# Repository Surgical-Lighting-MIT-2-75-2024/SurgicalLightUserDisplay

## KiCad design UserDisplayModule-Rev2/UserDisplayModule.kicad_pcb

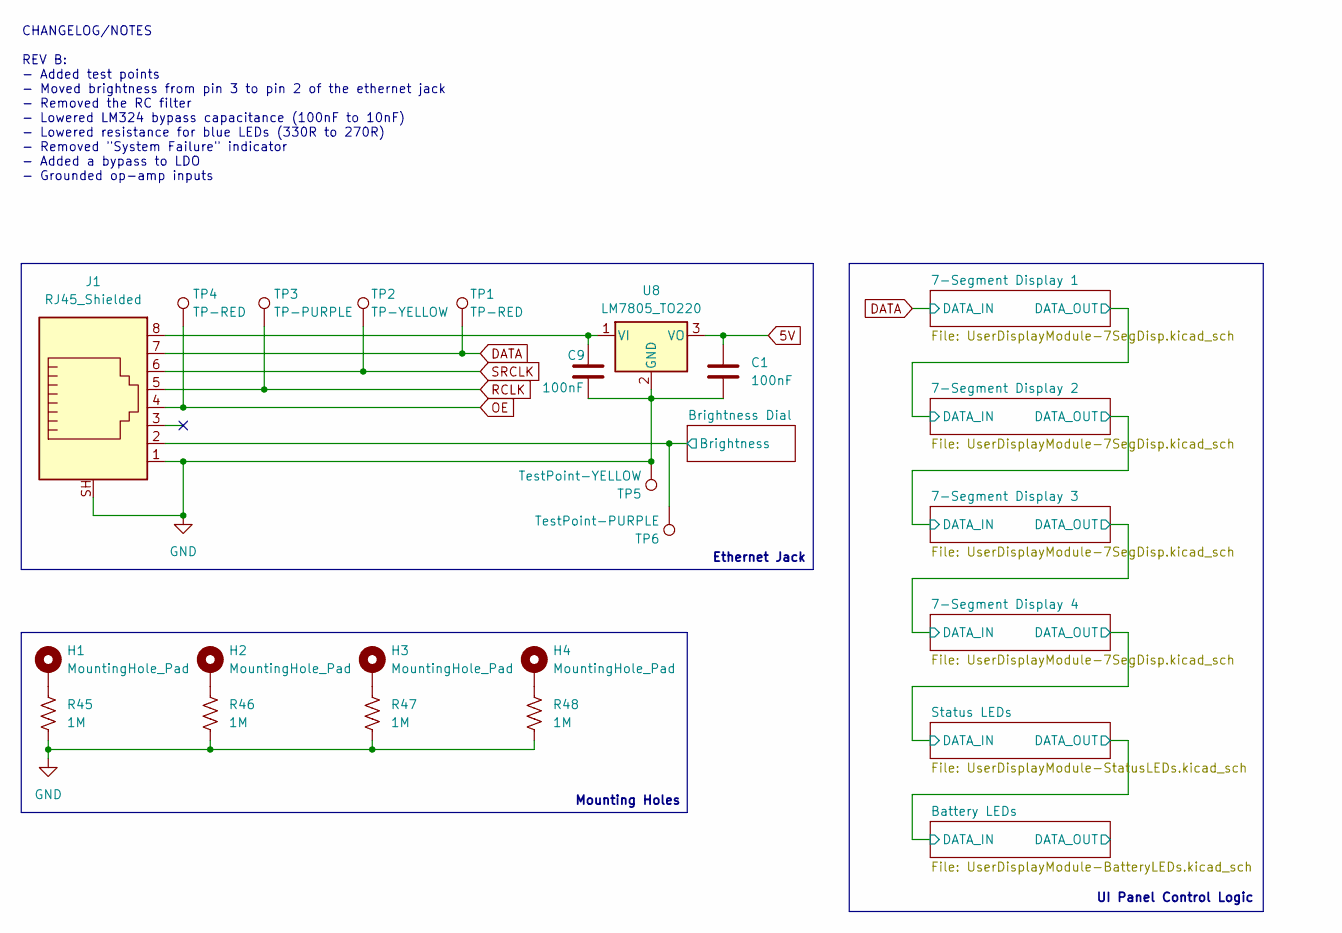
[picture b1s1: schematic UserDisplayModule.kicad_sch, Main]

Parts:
C1, C9: 100nF; C_0805_2012Metric
H1, H2, H3, H4: MountingHole_Pad; MountingHole_3.2mm_M3_Pad
J1: RJ45_Shielded; RJ45_Shielded_EthernetJack; Digikey PN AE10399-ND
R45, R46, R47, R48: 1M; R_0805_2012Metric; Digikey PN RMCF0805FT1M00CT-ND
TP1, TP4: TP-RED; TestPoint_Keystone_5000-5004_Miniature; Digikey PN 36-5260-ND
TP2: TP-YELLOW; TestPoint_Keystone_5000-5004_Miniature; Digikey PN 36-5264-ND
TP3: TP-PURPLE; TestPoint_Keystone_5000-5004_Miniature; Digikey PN 36-5269-ND
TP5: TestPoint-YELLOW; TestPoint_Keystone_5000-5004_Miniature; Digikey PN 36-5264-ND
TP6: TestPoint-PURPLE; TestPoint_Keystone_5000-5004_Miniature; Digikey PN 36-5269-ND
U8: LM7805_TO220; TO-220-3_Vertical; Digikey PN 2129-NJM7805FA-ND

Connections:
5V: C1.1, U8.3 (VO); also elsewhere on the board
/Brightness Dial/Brightness: J1.2, TP6.1; also elsewhere on the board
DATA: J1.7, TP1.1; also elsewhere on the board
GND: C1.2, C9.2, J1.1, J1.SH, R45.2, R46.2, R47.2, R48.2, TP5.1, U8.2 (GND); also elsewhere on the board
unnamed: H1.1, R45.1
unnamed: H2.1, R46.1
unnamed: H3.1, R47.1
unnamed: H4.1, R48.1
unnamed: C9.1, J1.8, U8.1 (VI)
OE: J1.4, TP4.1; also elsewhere on the board
RCLK: J1.5, TP3.1; also elsewhere on the board
SRCLK: J1.6, TP2.1; also elsewhere on the board

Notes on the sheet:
Mounting Holes
Ethernet Jack
UI Panel Control Logic
CHANGELOG/NOTES REV B: - Added test points - Moved brightness from pin 3 to pin 2 of the ethernet jack - Removed the RC filter - Lowered LM324 bypass capacitance (100nF to 10nF) - Lowered resistance for blue LEDs (330R to 270R) - Removed "System Failure" indicator - Added a bypass to LDO - Grounded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

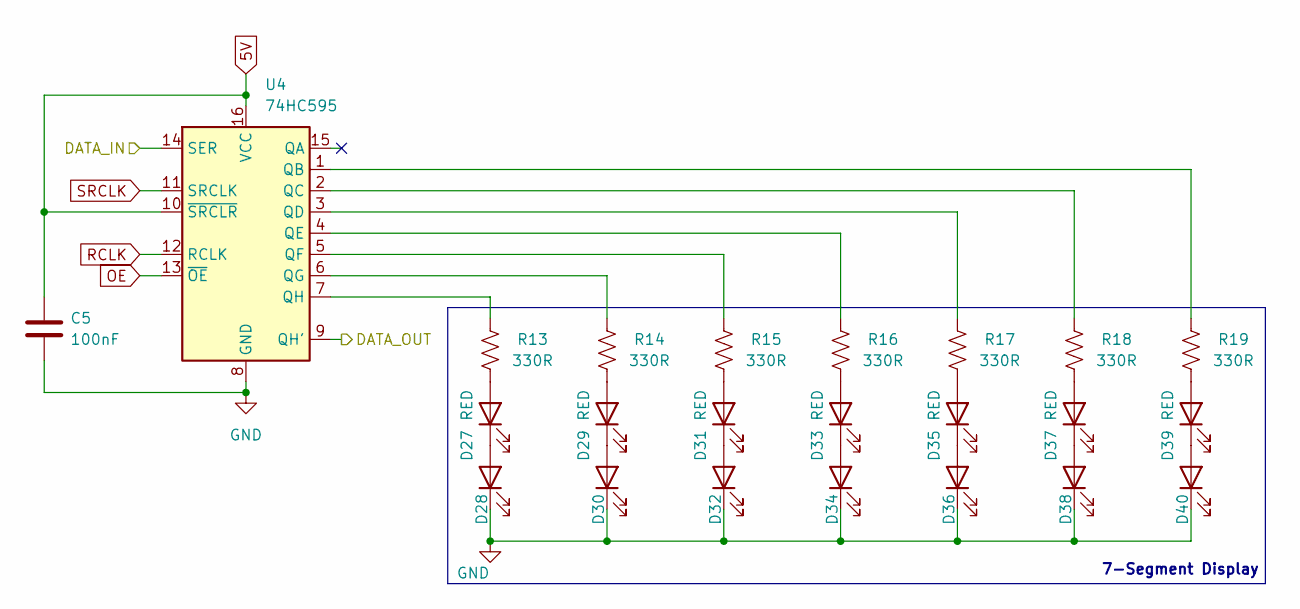
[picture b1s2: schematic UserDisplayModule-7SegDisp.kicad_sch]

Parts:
C5: 100nF; C_0805_2012Metric; Digikey PN 1276-1003-1-ND
D27, D28, D29, D30, D31, D32, D33, D34, D35, D36, D37, D38, D39, D40: RED; LED_0805_2012Metric; Digikey PN 732-4984-1-ND
R13, R14, R15, R16, R17, R18, R19: 330R; R_0805_2012Metric; Digikey PN RMCF0805FT330RCT-ND
U4: 74HC595; CD74HC595E; Digikey PN 296-1600-5-ND

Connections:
5V: C5.1, U4.10 (~SRCLR), U4.16 (VCC); also elsewhere on the board
/7-Segment Display 1/DATA_OUT: U4.9 (QH'); also elsewhere on the board
DATA: U4.14 (SER); also elsewhere on the board
GND: C5.2, D28.1 (K), D30.1 (K), D32.1 (K), D34.1 (K), D36.1 (K), D38.1 (K), D40.1 (K), U4.8 (GND); also elsewhere on the board
unnamed: D27.2 (A), R13.2
unnamed: D27.1 (K), D28.2 (A)
unnamed: D29.2 (A), R14.2
unnamed: D29.1 (K), D30.2 (A)
unnamed: D31.2 (A), R15.2
unnamed: D31.1 (K), D32.2 (A)
unnamed: D33.2 (A), R16.2
unnamed: D33.1 (K), D34.2 (A)
unnamed: D35.2 (A), R17.2
unnamed: D35.1 (K), D36.2 (A)
unnamed: D37.2 (A), R18.2
unnamed: D37.1 (K), D38.2 (A)
unnamed: D39.2 (A), R19.2
unnamed: D39.1 (K), D40.2 (A)
unnamed: R19.1, U4.1 (QB)
unnamed: R18.1, U4.2 (QC)
unnamed: R17.1, U4.3 (QD)
unnamed: R16.1, U4.4 (QE)
unnamed: R15.1, U4.5 (QF)
unnamed: R14.1, U4.6 (QG)
unnamed: R13.1, U4.7 (QH)
OE: U4.13 (~OE); also elsewhere on the board
RCLK: U4.12 (RCLK); also elsewhere on the board
SRCLK: U4.11 (SRCLK); also elsewhere on the board

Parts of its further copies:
C6, C7, C8: 100nF; C_0805_2012Metric; Digikey PN 1276-1003-1-ND
D46, D47, D48, D49, D50, D51, D52, D53, D54, D55, D56, D57, D58, D59, D60, D61, D62, D63, D64, D65, D66, D67, D68, D69, D70, D71, D72, D73, D74, D75, D76, D77, D78, D79, D80, D81, D82, D83, D84, D85, D86, D87: RED; LED_0805_2012Metric; Digikey PN 732-4984-1-ND
R24, R25, R26, R27, R28, R29, R30, R31, R32, R33, R34, R35, R36, R37, R38, R39, R40, R41, R42, R43, R44: 330R; R_0805_2012Metric; Digikey PN RMCF0805FT330RCT-ND
U3, U6, U7: 74HC595; CD74HC595E; Digikey PN 296-1600-5-ND

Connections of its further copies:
5V: C6.1, C7.1, C8.1, U3.10 (~SRCLR), U3.16 (VCC), U6.10 (~SRCLR), U6.16 (VCC), U7.10 (~SRCLR), U7.16 (VCC); also elsewhere on the board
/7-Segment Display 1/DATA_OUT: U3.14 (SER); also elsewhere on the board
/7-Segment Display 2/DATA_OUT: U3.9 (QH'), U6.14 (SER)
/7-Segment Display 3/DATA_OUT: U6.9 (QH'), U7.14 (SER)
/7-Segment Display 4/DATA_OUT: U7.9 (QH'); also elsewhere on the board
GND: C6.2, C7.2, C8.2, D47.1 (K), D49.1 (K), D51.1 (K), D53.1 (K), D55.1 (K), D57.1 (K), D59.1 (K), D61.1 (K), D63.1 (K), D65.1 (K), D67.1 (K), D69.1 (K), D71.1 (K), D73.1 (K), D75.1 (K), D77.1 (K), D79.1 (K), D81.1 (K), D83.1 (K), D85.1 (K), D87.1 (K), U3.8 (GND), U6.8 (GND), U7.8 (GND); also elsewhere on the board
unnamed: D46.2 (A), R24.2
unnamed: D46.1 (K), D47.2 (A)
unnamed: D48.2 (A), R25.2
unnamed: D48.1 (K), D49.2 (A)
unnamed: D50.2 (A), R26.2
unnamed: D50.1 (K), D51.2 (A)
unnamed: D52.2 (A), R27.2
unnamed: D52.1 (K), D53.2 (A)
unnamed: D54.2 (A), R28.2
unnamed: D54.1 (K), D55.2 (A)
unnamed: D56.2 (A), R29.2
unnamed: D56.1 (K), D57.2 (A)
unnamed: D58.2 (A), R30.2
unnamed: D58.1 (K), D59.2 (A)
unnamed: D60.2 (A), R31.2
unnamed: D60.1 (K), D61.2 (A)
unnamed: D62.2 (A), R32.2
unnamed: D62.1 (K), D63.2 (A)
unnamed: D64.2 (A), R33.2
unnamed: D64.1 (K), D65.2 (A)
unnamed: D66.2 (A), R34.2
unnamed: D66.1 (K), D67.2 (A)
unnamed: D68.2 (A), R35.2
unnamed: D68.1 (K), D69.2 (A)
unnamed: D70.2 (A), R36.2
unnamed: D70.1 (K), D71.2 (A)
unnamed: D72.2 (A), R37.2
unnamed: D72.1 (K), D73.2 (A)
unnamed: D74.2 (A), R38.2
unnamed: D74.1 (K), D75.2 (A)
unnamed: D76.2 (A), R39.2
unnamed: D76.1 (K), D77.2 (A)
unnamed: D78.2 (A), R40.2
unnamed: D78.1 (K), D79.2 (A)
unnamed: D80.2 (A), R41.2
unnamed: D80.1 (K), D81.2 (A)
unnamed: D82.2 (A), R42.2
unnamed: D82.1 (K), D83.2 (A)
unnamed: D84.2 (A), R43.2
unnamed: D84.1 (K), D85.2 (A)
unnamed: D86.2 (A), R44.2
unnamed: D86.1 (K), D87.2 (A)
unnamed: R30.1, U3.1 (QB)
unnamed: R29.1, U3.2 (QC)
unnamed: R28.1, U3.3 (QD)
unnamed: R27.1, U3.4 (QE)
unnamed: R26.1, U3.5 (QF)
unnamed: R25.1, U3.6 (QG)
unnamed: R24.1, U3.7 (QH)
unnamed: R37.1, U6.1 (QB)
unnamed: R36.1, U6.2 (QC)
unnamed: R35.1, U6.3 (QD)
unnamed: R34.1, U6.4 (QE)
unnamed: R33.1, U6.5 (QF)
unnamed: R32.1, U6.6 (QG)
unnamed: R31.1, U6.7 (QH)
unnamed: R44.1, U7.1 (QB)
unnamed: R43.1, U7.2 (QC)
unnamed: R42.1, U7.3 (QD)
unnamed: R41.1, U7.4 (QE)
unnamed: R40.1, U7.5 (QF)
unnamed: R39.1, U7.6 (QG)
unnamed: R38.1, U7.7 (QH)
OE: U3.13 (~OE), U6.13 (~OE), U7.13 (~OE); also elsewhere on the board
RCLK: U3.12 (RCLK), U6.12 (RCLK), U7.12 (RCLK); also elsewhere on the board
SRCLK: U3.11 (SRCLK), U6.11 (SRCLK), U7.11 (SRCLK); also elsewhere on the board

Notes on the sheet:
7-Segment Display

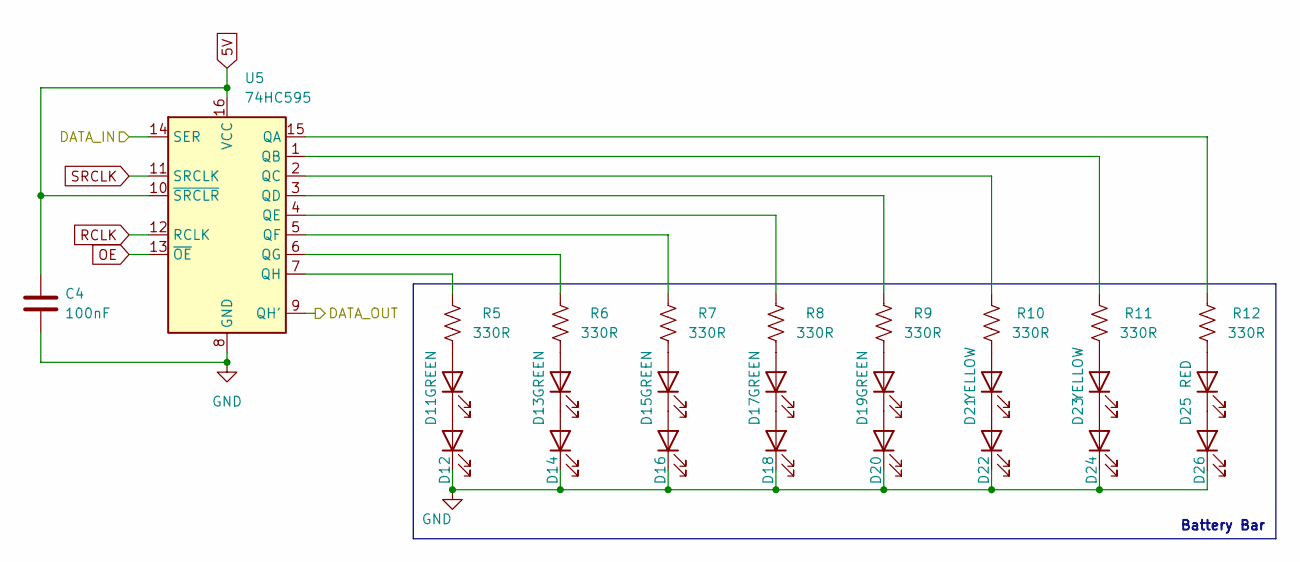
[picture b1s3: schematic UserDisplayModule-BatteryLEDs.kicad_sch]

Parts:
C4: 100nF; C_0805_2012Metric; Digikey PN 1276-1003-1-ND
D11, D12, D13, D14, D15, D16, D17, D18, D19, D20: GREEN; LED_0805_2012Metric; Digikey PN 732-4983-1-ND
D21, D22, D23, D24: YELLOW; LED_0805_2012Metric; Digikey PN 732-4987-1-ND
D25, D26: RED; LED_0805_2012Metric; Digikey PN 732-4984-1-ND
R5, R6, R7, R8, R9, R10, R11, R12: 330R; R_0805_2012Metric; Digikey PN RMCF0805FT330RCT-ND
U5: 74HC595; CD74HC595E; Digikey PN 296-1600-5-ND

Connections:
5V: C4.1, U5.10 (~SRCLR), U5.16 (VCC); also elsewhere on the board
/Battery LEDs/DATA_IN: U5.14 (SER); also elsewhere on the board
/Battery LEDs/DATA_OUT: U5.9 (QH')
GND: C4.2, D12.1 (K), D14.1 (K), D16.1 (K), D18.1 (K), D20.1 (K), D22.1 (K), D24.1 (K), D26.1 (K), U5.8 (GND); also elsewhere on the board
unnamed: D11.2 (A), R5.2
unnamed: D11.1 (K), D12.2 (A)
unnamed: D13.2 (A), R6.2
unnamed: D13.1 (K), D14.2 (A)
unnamed: D15.2 (A), R7.2
unnamed: D15.1 (K), D16.2 (A)
unnamed: D17.2 (A), R8.2
unnamed: D17.1 (K), D18.2 (A)
unnamed: D19.2 (A), R9.2
unnamed: D19.1 (K), D20.2 (A)
unnamed: D21.2 (A), R10.2
unnamed: D21.1 (K), D22.2 (A)
unnamed: D23.2 (A), R11.2
unnamed: D23.1 (K), D24.2 (A)
unnamed: D25.2 (A), R12.2
unnamed: D25.1 (K), D26.2 (A)
unnamed: R12.1, U5.15 (QA)
unnamed: R11.1, U5.1 (QB)
unnamed: R10.1, U5.2 (QC)
unnamed: R9.1, U5.3 (QD)
unnamed: R8.1, U5.4 (QE)
unnamed: R7.1, U5.5 (QF)
unnamed: R6.1, U5.6 (QG)
unnamed: R5.1, U5.7 (QH)
OE: U5.13 (~OE); also elsewhere on the board
RCLK: U5.12 (RCLK); also elsewhere on the board
SRCLK: U5.11 (SRCLK); also elsewhere on the board

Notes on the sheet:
Battery Bar

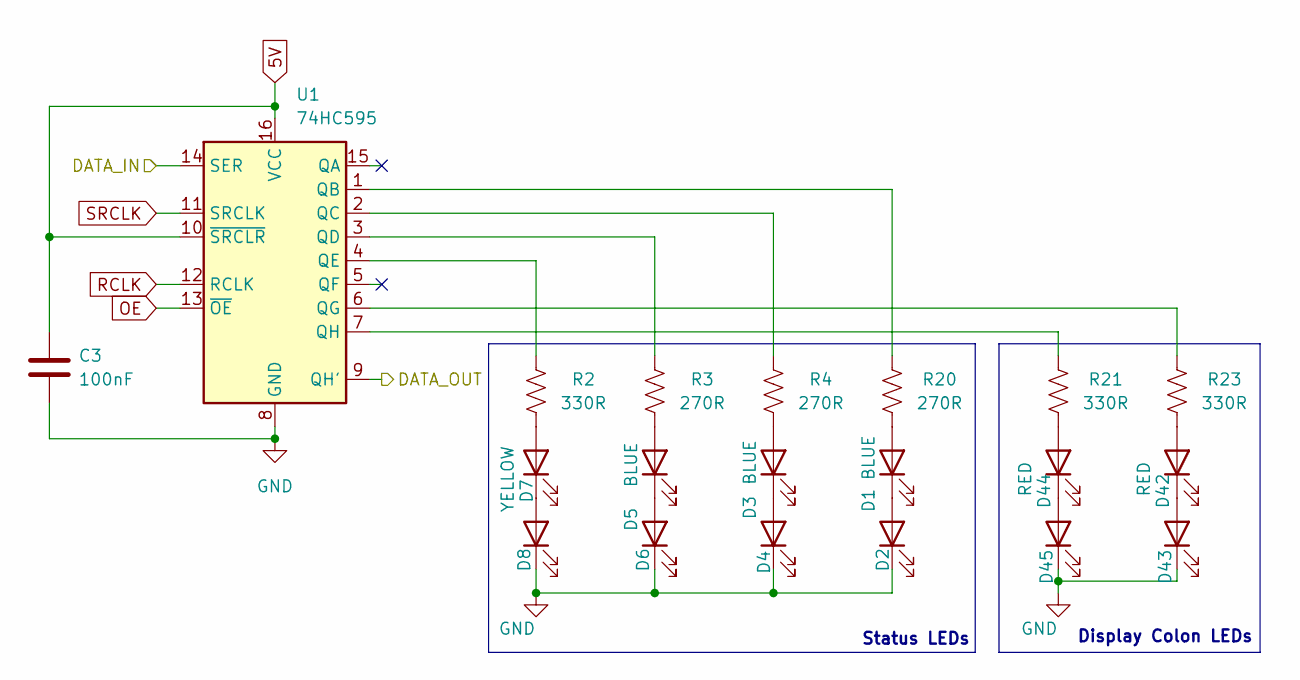
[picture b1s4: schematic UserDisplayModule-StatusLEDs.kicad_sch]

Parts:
C3: 100nF; C_0805_2012Metric; Digikey PN 1276-1003-1-ND
D1, D2, D3, D4, D5, D6: BLUE; LED_0805_2012Metric; Digikey PN 732-4982-1-ND
D7, D8: YELLOW; LED_0805_2012Metric; Digikey PN 732-4987-1-ND
D42, D43, D44, D45: RED; LED_0805_2012Metric; Digikey PN 732-4984-1-ND
R2, R21, R23: 330R; R_0805_2012Metric; Digikey PN RMCF0805FT330RCT-ND
R3, R4, R20: 270R; R_0805_2012Metric; Digikey PN RMCF0805FT330RCT-ND
U1: 74HC595; CD74HC595E; Digikey PN 296-1600-5-ND

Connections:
5V: C3.1, U1.10 (~SRCLR), U1.16 (VCC); also elsewhere on the board
/7-Segment Display 4/DATA_OUT: U1.14 (SER); also elsewhere on the board
/Battery LEDs/DATA_IN: U1.9 (QH'); also elsewhere on the board
GND: C3.2, D2.1 (K), D4.1 (K), D6.1 (K), D8.1 (K), D43.1 (K), D45.1 (K), U1.8 (GND); also elsewhere on the board
unnamed: D1.2 (A), R20.2
unnamed: D1.1 (K), D2.2 (A)
unnamed: D3.2 (A), R4.2
unnamed: D3.1 (K), D4.2 (A)
unnamed: D5.2 (A), R3.2
unnamed: D5.1 (K), D6.2 (A)
unnamed: D7.2 (A), R2.2
unnamed: D7.1 (K), D8.2 (A)
unnamed: D42.2 (A), R23.2
unnamed: D42.1 (K), D43.2 (A)
unnamed: D44.2 (A), R21.2
unnamed: D44.1 (K), D45.2 (A)
unnamed: R20.1, U1.1 (QB)
unnamed: R4.1, U1.2 (QC)
unnamed: R3.1, U1.3 (QD)
unnamed: R2.1, U1.4 (QE)
unnamed: R23.1, U1.6 (QG)
unnamed: R21.1, U1.7 (QH)
OE: U1.13 (~OE); also elsewhere on the board
RCLK: U1.12 (RCLK); also elsewhere on the board
SRCLK: U1.11 (SRCLK); also elsewhere on the board

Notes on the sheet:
Status LEDs
Display Colon LEDs

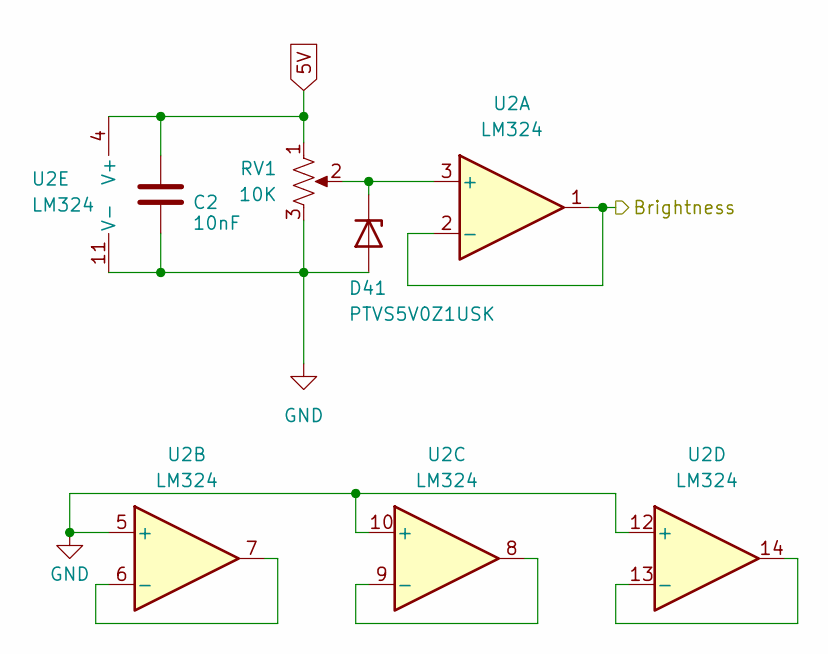
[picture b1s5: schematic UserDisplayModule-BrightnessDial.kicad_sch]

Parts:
C2: 10nF; C_0805_2012Metric; Digikey PN 1276-1003-1-ND
D41: PTVS5V0Z1USK; Nexperia_DSN1608-2_1.6x0.8mm; Digikey PN 1727-2742-1-ND
RV1: 10K; Potentiometer_TT_P0915N; Digikey PN 987-1649-ND
U2: LM324; DIP-14_W7.62mm; Digikey PN 296-1391-5-ND

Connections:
5V: C2.1, RV1.1, U2.4 (V+); also elsewhere on the board
/Brightness Dial/Brightness: U2.1, U2.2 (-); also elsewhere on the board
GND: C2.2, D41.2 (A), RV1.3, U2.5 (+), U2.10 (+), U2.11 (V-), U2.12 (+); also elsewhere on the board
unnamed: D41.1 (K), RV1.2, U2.3 (+)
unnamed: U2.6 (-), U2.7
unnamed: U2.8, U2.9 (-)
unnamed: U2.13 (-), U2.14

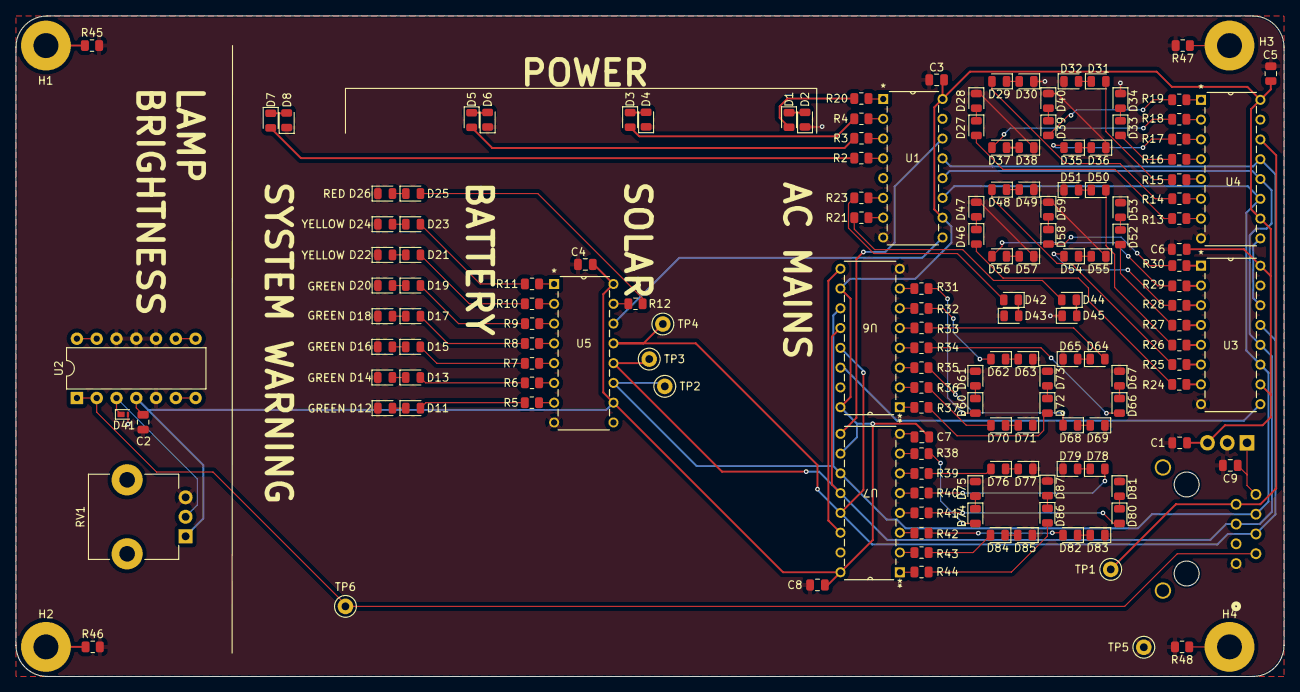
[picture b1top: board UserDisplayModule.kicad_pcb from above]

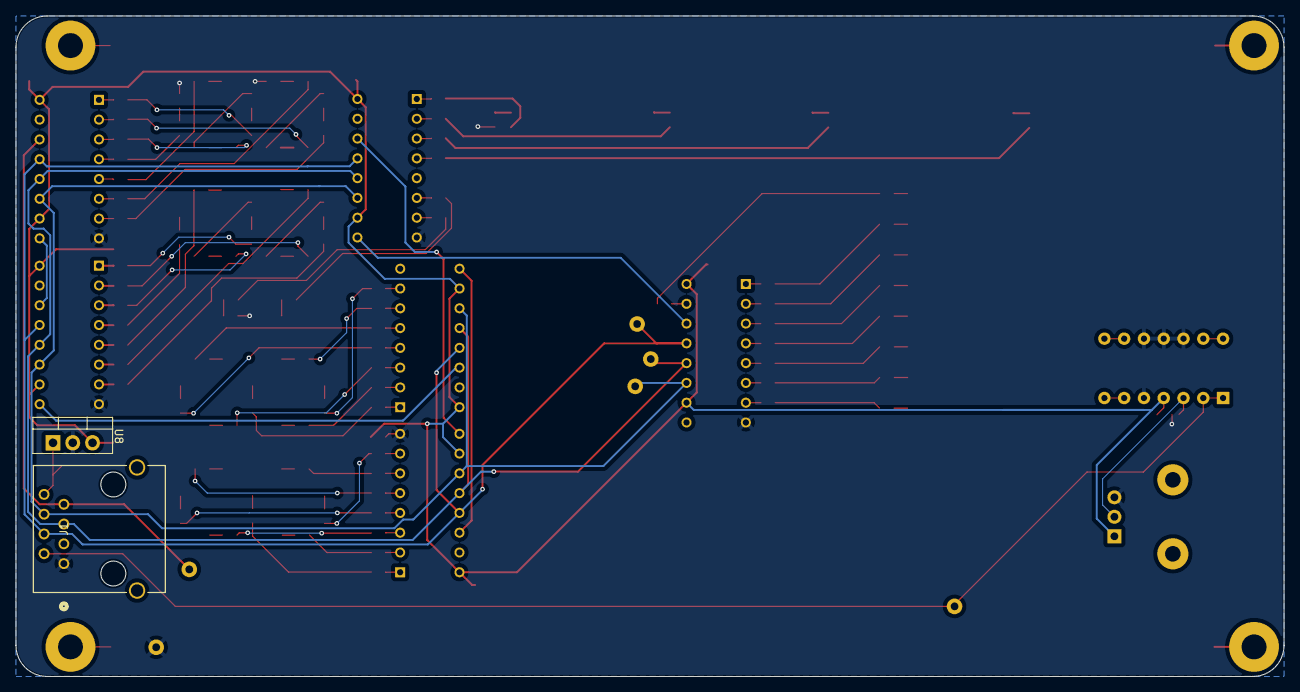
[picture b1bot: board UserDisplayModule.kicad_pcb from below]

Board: 2 copper layers, 162.8 x 84.8 mm, 160 parts (2 on the bottom side), 147 nets.

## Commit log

2024-03-23 started user display module schematic
2024-03-26 finished schematic + addressed comments
2024-03-28 doubled LEDs + started PCB
2024-03-28 started routing (help)
2024-03-29 finished routing pcb (minus ground pour)
2024-03-29 added ground pour + finished routing
2024-04-01 added 3d models, fixed footprints, finished routing
2024-04-03 added digikey pns
2024-04-03 Edited BOM for R/C parts
2024-04-03 added digikey PNs to diode and pot
2024-04-24 added rev 2
2024-04-24 more changes: ldo bypass + grounding op amp
